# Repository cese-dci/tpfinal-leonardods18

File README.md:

TP Diseño de Circuitos Impresos [CESE 10Co2019]

Autor: Del Sancio Leonardo Daniel   -  Alumno revisor: Yapura Alberto  - Docente Revisor: Diego Brengi

Nombre del proyecto: MÓDEM ENERGY METER
Descripción del proyecto: Este proyecto consiste en tomar lecturas de tensión y corrientes de equipos trifásicos y trasnsmitirlas por 
Wifi o bluetooth, el circuito integrado ATM90E36 es el encargado de tomar las variables físicas y trasmitirlas al ESP32 por SPI.

------------------------------------------------------------------------------------
El diseño se Realizará en la empresa fabricante de PCB JLCPCB. https://jlcpcb.com/#

En esta página podes realizar prototipos de excelente calidad por 2 dolares. 

------------------------------------------------------------------------------------

NOTA: en el archivo BOM se pueden encontrar todos los componentes y su fabricante de la página MOUSER. 
https://ar.mouser.com/

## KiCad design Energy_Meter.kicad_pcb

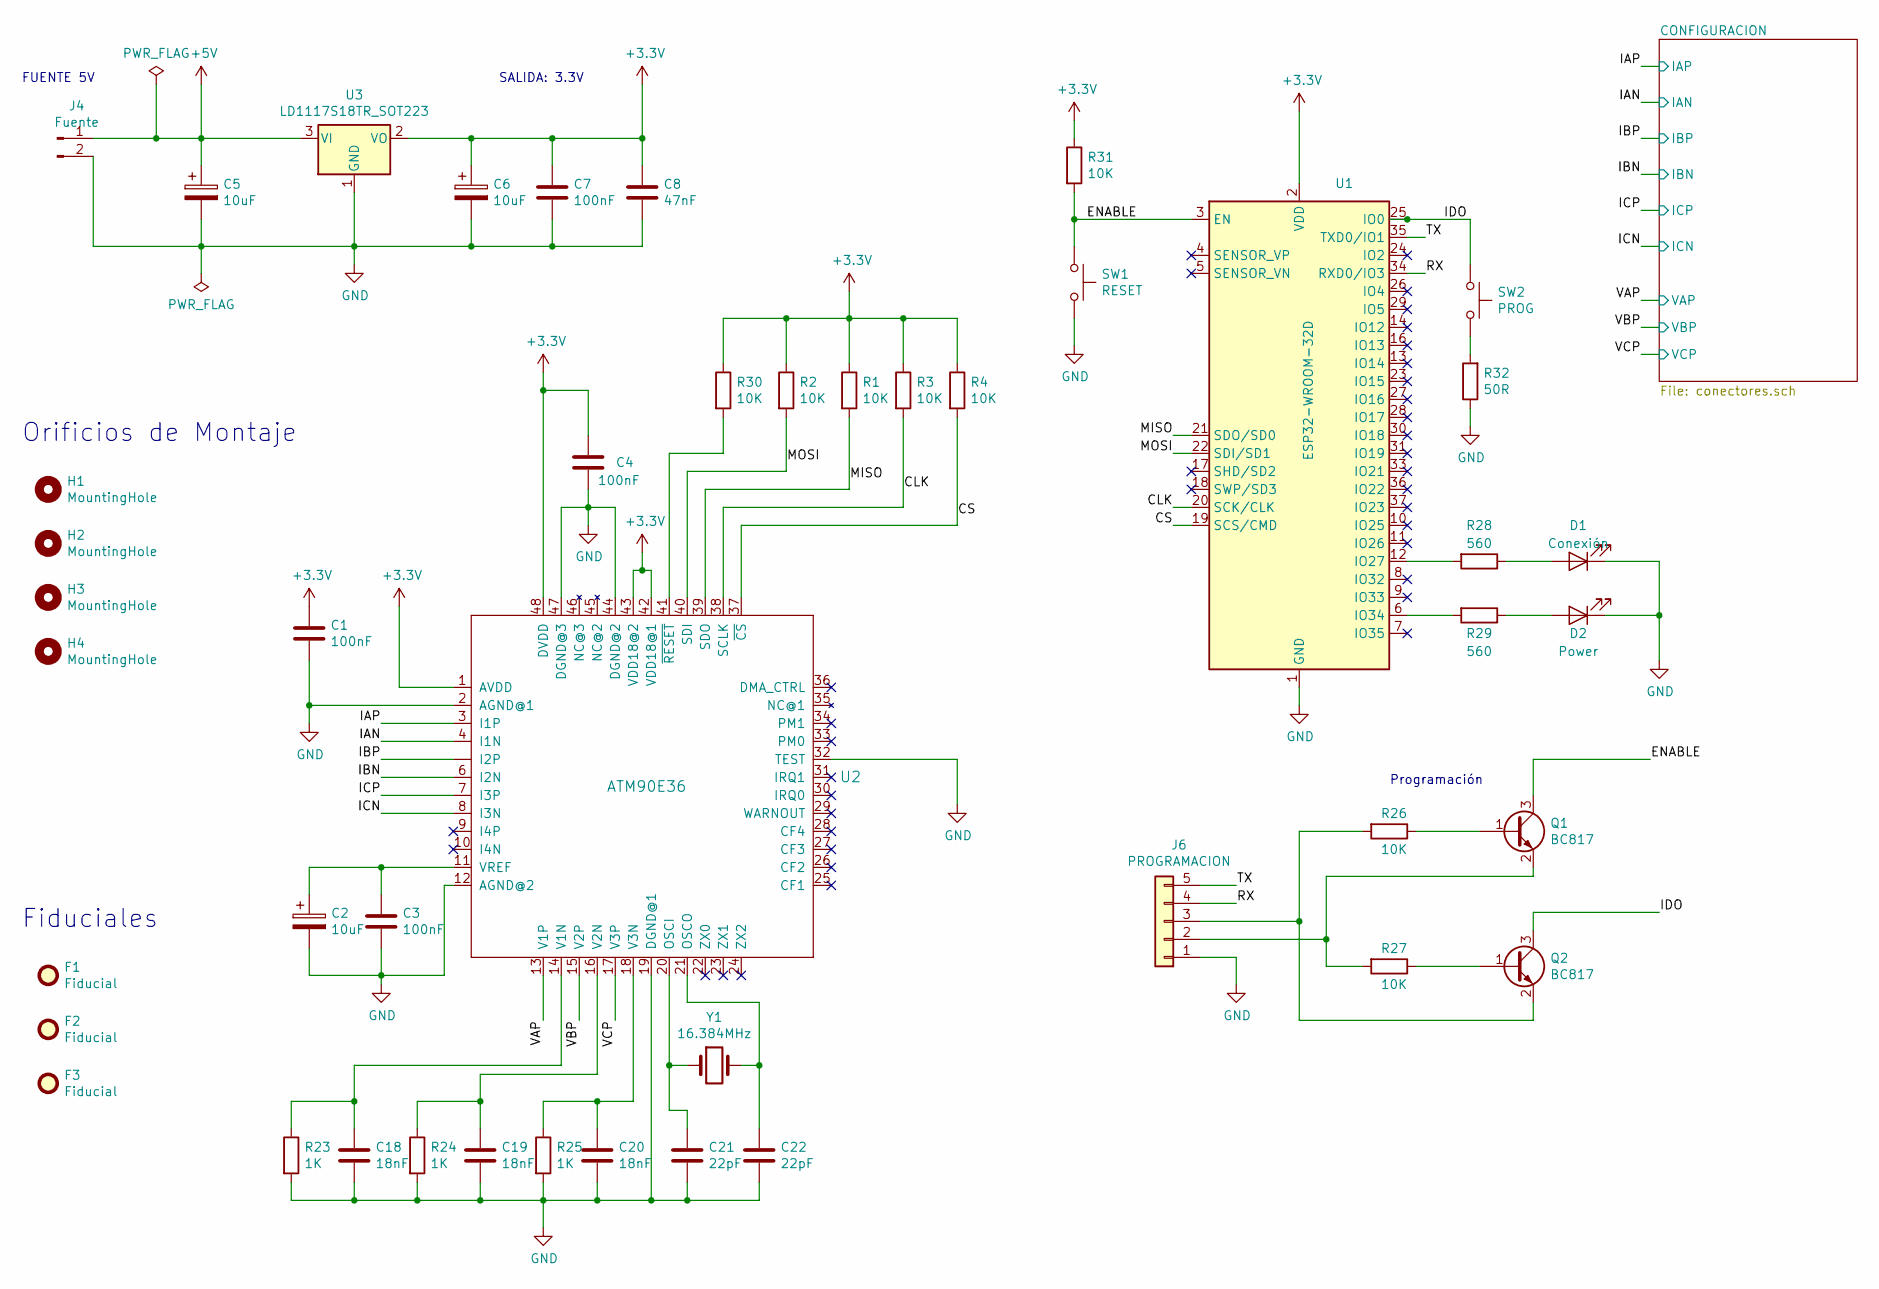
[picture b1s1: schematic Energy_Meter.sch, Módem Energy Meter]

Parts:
C1, C3, C4, C7: 100nF; C_0805_2012Metric
C2, C5, C6: 10uF; CP_Elec_5x5.3
C8: 47nF; C_0805_2012Metric
C18, C19, C20: 18nF; C_0805_2012Metric
C21, C22: 22pF; C_0805_2012Metric
D1: Conexión; LED_0805_2012Metric
D2: Power; LED_0805_2012Metric
F1, F2, F3: Fiducial; Fiducial_0.5mm_Mask1.5mm
H1, H2, H3, H4: MountingHole; MountingHole_2.2mm_M2_Pad_Via
J4: Fuente; Molex_KK-254_AE-6410-02A_1x02_P2.54mm_Vertical
J6: PROGRAMACION; PinHeader_1x05_P2.54mm_Vertical
Q1: BC817; SOT-23; Mouser 771-BC817K-40HVL
Q2: BC817; SOT-23; Mouser 771-BC817K-16HR
R1, R2, R3, R4, R26, R27, R30, R31: 10K; R_0805_2012Metric
R23, R24, R25: 1K; R_0805_2012Metric
R28, R29: 560; R_0805_2012Metric
R32: 50R; R_0805_2012Metric
SW1: RESET; SW_PUSH_6mm_H4.3mm
SW2: PROG; SW_PUSH_6mm_H4.3mm
U1: ESP32-WROOM-32D; ESP32-WROOM-32; Mouser 356-ESP32WRM32E132PH
U2: ATM90E36; TQFP-48_7x7mm_P0.5mm; Mouser 556-ATM90E36A-AU-Y
U3: LD1117S18TR_SOT223; SOT-223-3_TabPin2; Mouser 511-LD1117AS18
Y1: 16.384MHz; Crystal_HC49-4H_Vertical; Digikey XC2790TR-ND

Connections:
+3V3: C1.1, C4.1, C6.1, C7.1, C8.1, R1.1, R2.1, R3.1, R4.1, R30.1, R31.1, U1.2 (VDD), U2.1 (AVDD), U2.42 (VDD18@1), U2.43 (VDD18@2), U2.48 (DVDD), U3.2 (VO)
+5V: C5.1, J4.1, U3.3 (VI)
/CLK: R3.2, U1.20 (SCK/CLK), U2.38 (SCLK)
/CS: R4.2, U1.19 (SCS/CMD), U2.37 (~CS)
/ENABLE: Q1.3 (C), R31.2, SW1.1, U1.3 (EN)
/IAN: U2.4 (I1N); also elsewhere on the board
/IAP: U2.3 (I1P); also elsewhere on the board
/IBN: U2.6 (I2N); also elsewhere on the board
/IBP: U2.5 (I2P); also elsewhere on the board
/ICN: U2.8 (I3N); also elsewhere on the board
/ICP: U2.7 (I3P); also elsewhere on the board
/IDO: Q2.3 (C), SW2.1, U1.25 (IO0)
/MISO: R1.2, U1.21 (SDO/SD0), U2.39 (SDO)
/MOSI: R2.2, U1.22 (SDI/SD1), U2.40 (SDI)
/RX: J6.4, U1.34 (RXD0/IO3)
/TX: J6.5, U1.35 (TXD0/IO1)
/VAP: U2.13 (V1P); also elsewhere on the board
/VBP: U2.15 (V2P); also elsewhere on the board
/VCP: U2.17 (V3P); also elsewhere on the board
GND: C1.2, C2.2, C3.2, C4.2, C5.2, C6.2, C7.2, C8.2, C18.2, C19.2, C20.2, C21.2, C22.2, D1.1 (K), D2.1 (K), J4.2, J6.1, R23.2, R24.2, R25.2, R32.1, SW1.2, U1.1 (GND), U1.15 (GND), U1.38 (GND), U1.39 (GND), U2.2 (AGND@1), U2.12 (AGND@2), U2.19 (DGND@1), U2.32 (TEST), U2.44 (DGND@2), U2.47 (DGND@3), U3.1 (GND); also elsewhere on the board
unnamed: C2.1, C3.1, U2.11 (VREF)
unnamed: C18.1, R23.1, U2.14 (V1N)
unnamed: C19.1, R24.1, U2.16 (V2N)
unnamed: C20.1, R25.1, U2.18 (V3N)
unnamed: C21.1, U2.20 (OSCI), Y1.1
unnamed: C22.1, U2.21 (OSCO), Y1.2
unnamed: D1.2 (A), R28.1
unnamed: D2.2 (A), R29.1
unnamed: J6.2, Q1.2 (E), R27.2
unnamed: J6.3, Q2.2 (E), R26.2
unnamed: Q1.1 (B), R26.1
unnamed: Q2.1 (B), R27.1
unnamed: R28.2, U1.12 (IO27)
unnamed: R29.2, U1.6 (IO34)
unnamed: R30.2, U2.41 (~RESET)
unnamed: R32.2, SW2.2

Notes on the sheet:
Programación
SALIDA: 3.3V
FUENTE 5V
Orificios de Montaje
Fiduciales

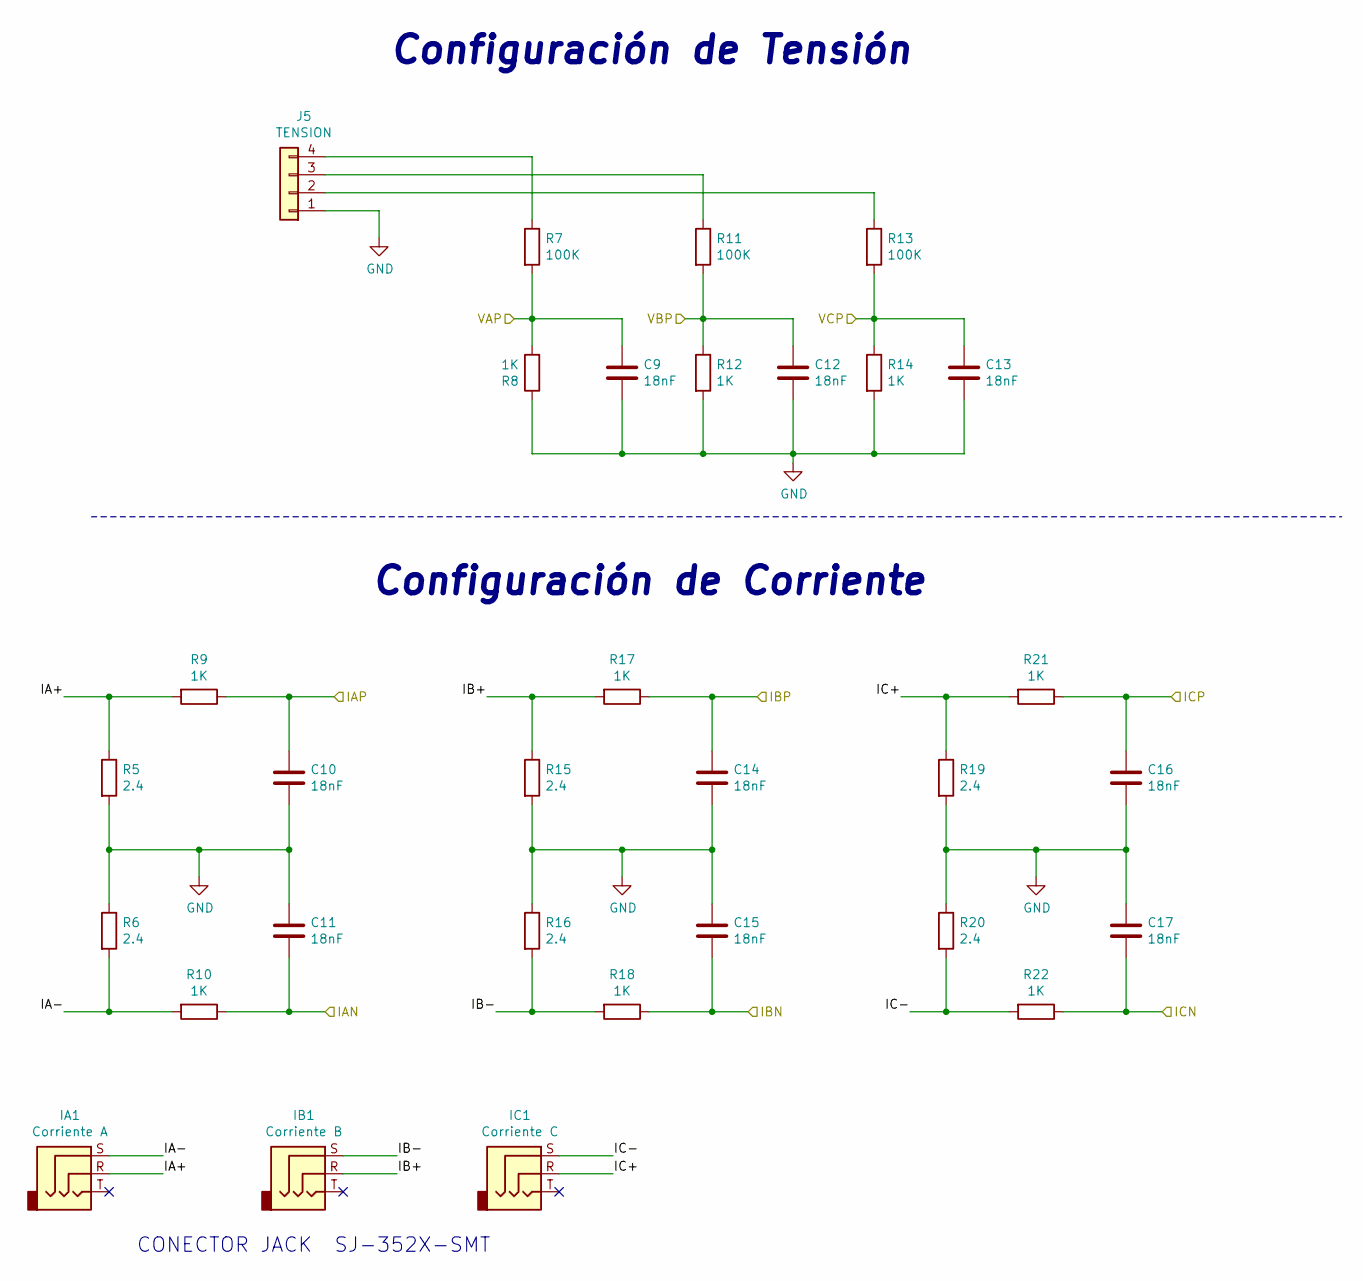
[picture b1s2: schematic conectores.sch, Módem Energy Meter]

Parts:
C9, C10, C11, C12, C13, C14, C15, C16, C17: 18nF; C_0805_2012Metric
IA1: Corriente A; Jack_3.5mm_CUI_SJ-3523-SMT_Horizontal
IB1: Corriente B; Jack_3.5mm_CUI_SJ-3523-SMT_Horizontal
IC1: Corriente C; Jack_3.5mm_CUI_SJ-3523-SMT_Horizontal
J5: TENSION; Molex_KK-254_AE-6410-04A_1x04_P2.54mm_Vertical
R5, R6, R15, R16, R19, R20: 2.4; R_0805_2012Metric
R7, R11, R13: 100K; R_0805_2012Metric
R8, R9, R10, R12, R14, R17, R18, R21, R22: 1K; R_0805_2012Metric

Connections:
/CONFIGURACION/IA+: IA1.R, R5.1, R9.2; also elsewhere on the board
/CONFIGURACION/IA-: IA1.S, R6.2, R10.2; also elsewhere on the board
/CONFIGURACION/IB+: IB1.R, R15.1, R17.2; also elsewhere on the board
/CONFIGURACION/IB-: IB1.S, R16.2, R18.2; also elsewhere on the board
/CONFIGURACION/IC+: IC1.R, R19.1, R21.2; also elsewhere on the board
/CONFIGURACION/IC-: IC1.S, R20.2, R22.2; also elsewhere on the board
/IAN: C11.2, R10.1; also elsewhere on the board
/IAP: C10.1, R9.1; also elsewhere on the board
/IBN: C15.2, R18.1; also elsewhere on the board
/IBP: C14.1, R17.1; also elsewhere on the board
/ICN: C17.2, R22.1; also elsewhere on the board
/ICP: C16.1, R21.1; also elsewhere on the board
/VAP: C9.1, R7.2, R8.2; also elsewhere on the board
/VBP: C12.1, R11.2, R12.1; also elsewhere on the board
/VCP: C13.1, R13.2, R14.1; also elsewhere on the board
GND: C9.2, C10.2, C11.1, C12.2, C13.2, C14.2, C15.1, C16.2, C17.1, J5.1, R5.2, R6.1, R8.1, R12.2, R14.2, R15.2, R16.1, R19.2, R20.1; also elsewhere on the board
unnamed: J5.2, R13.1
unnamed: J5.3, R11.1
unnamed: J5.4, R7.1

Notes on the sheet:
Configuración de Tensión
CONECTOR JACK SJ-352X-SMT
Configuración de Corriente

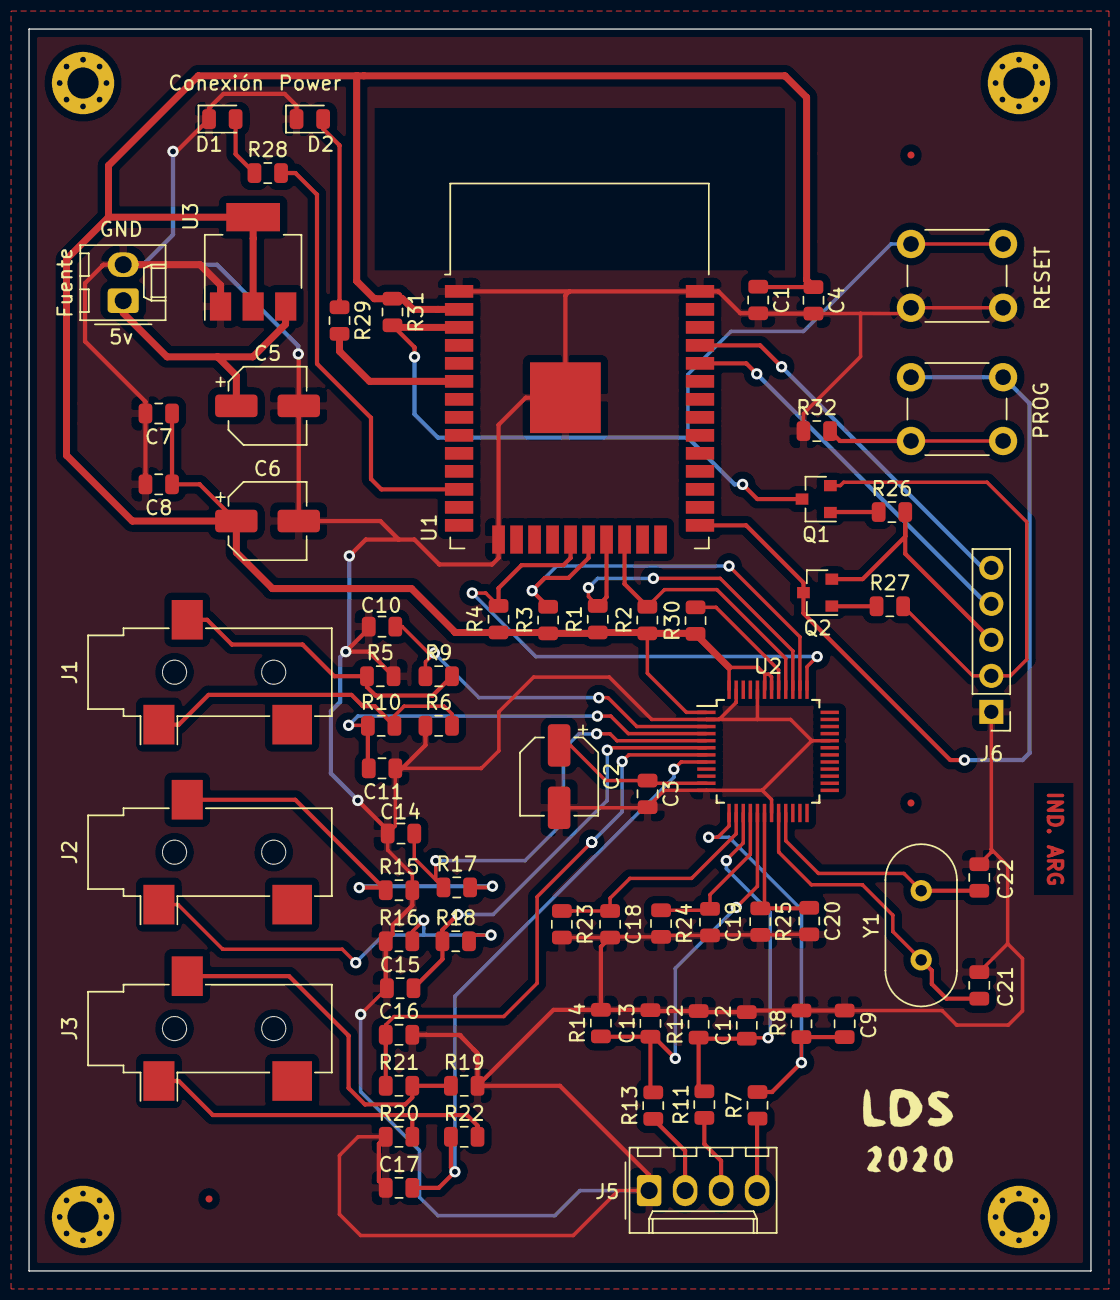
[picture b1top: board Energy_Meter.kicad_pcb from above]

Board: 2 copper layers, 74.9 x 87.6 mm, 77 parts (0 on the bottom side), 45 nets.

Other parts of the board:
J1: Corriente A; Jack_3.5mm_CUI_SJ-3523-SMT_Horizontal
J2: Corriente B; Jack_3.5mm_CUI_SJ-3523-SMT_Horizontal
J3: Corriente C; Jack_3.5mm_CUI_SJ-3523-SMT_Horizontal

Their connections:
/CONFIGURACION/IA+: J1.R; also elsewhere on the board
/CONFIGURACION/IA-: J1.S; also elsewhere on the board
/CONFIGURACION/IB+: J2.R; also elsewhere on the board
/CONFIGURACION/IB-: J2.S; also elsewhere on the board
/CONFIGURACION/IC+: J3.R; also elsewhere on the board
/CONFIGURACION/IC-: J3.S; also elsewhere on the board

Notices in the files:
Energy_Meter.kicad_pcb:
License: CC BY 4.0
